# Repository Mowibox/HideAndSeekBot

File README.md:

# HideAndSeekBot
The project consists of designing a robot able to play Hide & Seek with another one.

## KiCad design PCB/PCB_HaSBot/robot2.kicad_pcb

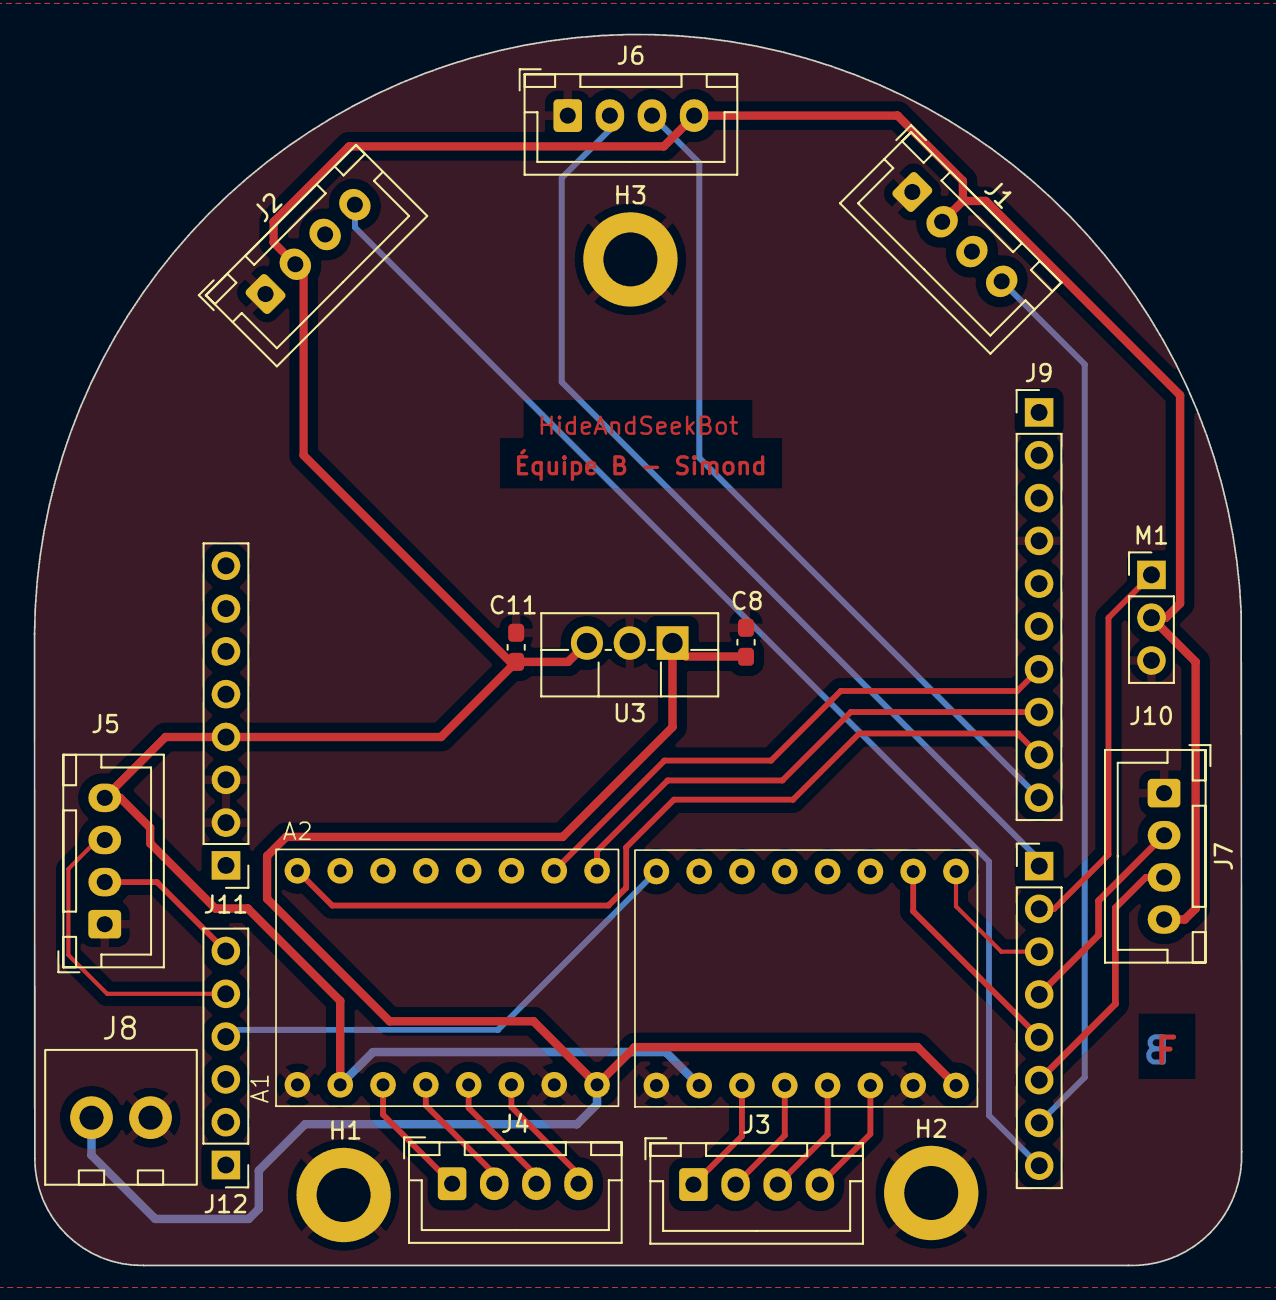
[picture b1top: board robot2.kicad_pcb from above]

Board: 2 copper layers, 71.6 x 73.0 mm, 21 parts (0 on the bottom side), 26 nets.

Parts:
A1, A2: Pololu_Breakout_A4988; Motor_Driver
C8: 0.33u; C_0603_1608Metric_Pad1.08x0.95mm_HandSolder
C11: 0.1u; C_0603_1608Metric_Pad1.08x0.95mm_HandSolder
H1, H2, H3: MountingHole_Pad; MountingHole_3.2mm_M3_DIN965_Pad
J1, J2, J3, J4, J5, J6, J7: Conn_01x04; JST_XH_B4B-XH-A_1x04_P2.50mm_Vertical
J8: Screw_Terminal_01x02; 180G-2-vertical
J9: Conn_01x10; PinHeader_1x10_P2.54mm_Vertical
J10, J11: Conn_01x08; PinHeader_1x08_P2.54mm_Vertical
J12: Conn_01x06; PinHeader_1x06_P2.54mm_Vertical
M1: Motor_Servo; PinHeader_1x03_P2.54mm_Vertical
U3: L7805; TO-220F-3_Vertical

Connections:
1A_M1: A1.4 (1A), J4.2
1A_M2: A2.4 (1A), J3.2
1B_M1: A1.3 (1B), J4.1
1B_M2: A2.3 (1B), J3.1
2A_M1: A1.5 (2A), J4.3
2A_M2: A2.5 (2A), J3.3
2B_M1: A1.6 (2B), J4.4
2B_M2: A2.6 (2B), J3.4
+5V: A1.2 (VDD), A2.2 (VDD), C11.1, J1.2, J2.2, J5.4, J6.4, J7.4, J11.4, M1.2 (+), U3.3 (OUT)
+9V: A1.8 (VMOT), A2.8 (VMOT), C8.1, J8.1, U3.1 (IN)
DIR_M1: A1.16 (DIR), J9.8
DIR_M2: A2.16 (DIR), J10.3
ENABLE_M1: A1.9 (~ENABLE), J9.9
ENABLE_M2: A2.9 (~ENABLE), J12.4
Echo1: J5.2, J12.6
Echo2: J6.2, J10.1
Echo3: J7.2, J10.4
GND: A1.1 (GND), A1.7 (GND), A2.1 (GND), A2.7 (GND), C8.2, C11.2, H1.1, H2.1, H3.1, J1.1, J2.1, J5.1, J6.1, J7.1, J8.2, J9.4, J11.2, J11.3, M1.3 (-), U3.2 (GND)
RX: J2.4, J10.8
SERVO: J10.2, M1.1 (PWM)
STEP_M1: A1.15 (STEP), J9.7
STEP_M2: A2.15 (STEP), J10.5
TX: J1.4, J10.7
Trig1: J5.3, J12.5
Trig2: J6.3, J9.10
Trig3: J7.3, J10.6

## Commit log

2023-04-21 Ajout des premiers dossiers
2023-04-22 C'était un test
2023-04-22 Modification sur les instructions
2023-04-22 Suppression de l'exemple
2023-05-09 Ajout d'un code se cacher (test)
    creation d'un 1er code pour se cacher (sans stm32)
2023-05-09 ajout du code chercher 09/05
    à terminer, à fusionner avec les autres
2023-05-09 ajout des fonctions Rotate, TurnAngle, et modif MoveForward
    modification dans se cacher (test)
2023-05-11 Amélioration chercher
    Fin du code, ajout de la dimension temporelle
2023-05-11 Ajout des fichiers permettant de contrôler le moteur pas à pas
2023-05-11 Ajout du code pour capteur ultrason
2023-05-11 Ajout du code du capteur ultrason
2023-05-16 Modification code (test) Se Cacher
    - simplification du code
    - ne compte plus le nombre de tour autour d'un mur car il n'y a que des structures en L
2023-05-16 modification hide.c
2023-05-16 petite modif ligne 76 dans hide.c
2023-05-23 Ajout du PCB
2023-05-23 Creation simulation Python/pygame pour se cacher
2023-05-23 Python : Simulation du terrain de jeu
    - bordures et 4 murs en L d'orientation aléatoire
2023-05-23 Version 2.0 du PCB
2023-05-23 Version finale du pcb
2023-05-24 python : implementation d'un robot
    - robot représenté par un cercle rouge
    - se deplace dans 8 directions
    - debut d'algorithme de collision avec les murs (beaucoup de bug)
    -spawn pour le moment arbitrairement au centre de la map
2023-05-24 python : correction du bug d'affichage du labyrinthe
2023-05-30 python : mise en place capteur US
    Capteur US mis en place
2023-05-30 python : recherche sur le mouvement du robot
    triangle qui se deplace : peut tourner dans toutes les directions et avancer
2023-05-30 update python
2023-05-31 Correction du PCB
2023-06-01 pythonon : le robot se cache !
    incroyable mais vrai
2023-06-01 python : le robot se cache à 99% sans bug
    maintenant il arrive a faire le tour des murs et se cachera TOUJOURS dans un bel angle à l'abri des radars infrarouges
2023-06-04 Ajout du code final
2024-11-27 Updating .gitignore
